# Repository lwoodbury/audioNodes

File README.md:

# audioNodes
Raspberry Pi based Smart Speaker Network designed to run Pure Data patches for sonic arts. 

- small and fairly powerful with good audio quality (I2S 3W amplifier)
- contains a Lipo battery and manages charging via USB micro
- has a smart power switch (safe shutdown and power off)
- everything shared here under Creative Commons Attribution-ShareAlike 4.0 International License, the Raspberry Pi image *, laser cut designs, code and circuit designs. The safe shutdown circuitry and code are inspired by the NeonHorizon/lipopi repo which is covered by a GPL 3.0 licence. Go forth and prosper...

<br />This work is licensed under a <a rel="license" href="http://creativecommons.org/licenses/by-sa/4.0/">Creative Commons Attribution-ShareAlike 4.0 International License</a>.

The idea is to run audio nodes that can communicate with each other using OSC in PD and eventually add sensors and microphone input (and possibly some extra output functionality). The hardware is a development from my digital 'birds' installation: https://www.dotlib.org/home#/forest-of-imagination-2018/

This project is at an early stage and the documentation is not yet as clear as it could be, I have just taken on a new full time job and am not sure when I can next update it or add details on the OSC communication part. Happpy to accept any help in this respect!

To build your own, check out the BOM (bill of materials) spreadsheet for required components and follow the 'Building an Audio Node' document with reference to the 'build stage photos' and notes. The lasercut designs make use of a deep engrave to go around some of the components, you will have to work this out based on your material and laser cutter model.

* Raspberry Pi image can be download from here: https://www.dropbox.com/s/5uapjz6rh7yxo8m/raspbianImage.img.zip?dl=1

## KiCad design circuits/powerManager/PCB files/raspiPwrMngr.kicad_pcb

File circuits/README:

The power management circuit and code was inspired by NeonHorizon's 'lipopi' repo:
https://github.com/NeonHorizon/lipopi

Included here is a stripboard version and a PCB version, currently the case designs are based on the stripboard version. 

Use the file here to make new PCBs; unfortunately the original version of the KiCad project was lost but you can make new gerbers from this one:
..\circuits\powerManager\PCB files\Recovered_LiPoPiShutdown\LiPoPiShutdown.kicad_pcb

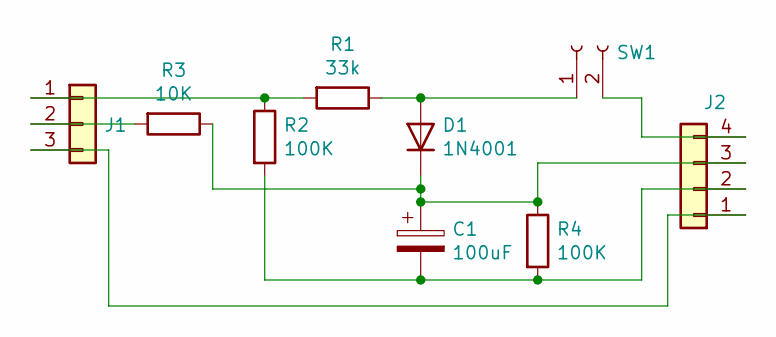
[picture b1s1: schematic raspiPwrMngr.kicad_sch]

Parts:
C1: 100uF; CP_Radial_D8.0mm_P5.00mm
D1: 1N4001; D_DO-41_SOD81_P10.16mm_Horizontal
J1: Conn_01x03; JST_PH_S3B-PH-K_1x03_P2.00mm_Horizontal
J2: Conn_01x04; JST_PH_S4B-PH-K_1x04_P2.00mm_Horizontal
R1: 33k; R_Axial_DIN0207_L6.3mm_D2.5mm_P10.16mm_Horizontal
R2, R4: 100K; R_Axial_DIN0207_L6.3mm_D2.5mm_P10.16mm_Horizontal
R3: 10K; R_Axial_DIN0207_L6.3mm_D2.5mm_P10.16mm_Horizontal
SW1: Conn_01x02_Socket; JST_PH_S2B-PH-K_1x02_P2.00mm_Horizontal

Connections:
unnamed: D1.2 (A), R1.1, SW1.1
unnamed: C1.1, D1.1 (K), J2.3, R3.1, R4.1
unnamed: J1.1, R1.2, R2.1
unnamed: J1.2, R3.2
unnamed: J1.3, J2.1
unnamed: C1.2, J2.2, R2.2, R4.2
unnamed: J2.4, SW1.2

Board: 2 copper layers, 9 parts (0 on the bottom side), 7 nets, no tracks yet.

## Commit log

2020-03-06 First commit
    Need to add support for lfs so can include raspbian image, or just host somewhere
2020-04-23 Added photos
2020-04-23 Update readme
    Add photos and text
2025-06-28 Update circuits with PCB version
    Use the file here to make new PCBs, unfortunately the original version of the KiCad project was lost but you can make new gerbers from this one:
    ..\circuits\powerManager\PCB files\Recovered_LiPoPiShutdown\LiPoPiShutdown.kicad_pcb
2025-07-23 Updated case designs
    Tidied up and archived old files
    Created new svg and cdr files in preparation for power manager pcb
2025-07-23 Update caseUpdated.svg
    Fixed layer order, in prep for power manage pcb
2025-07-24 Rescaled case design
    Seems there was a slight issue with scaling, have rescaled case outer diameter to 85mm
2025-07-27 Created PCB case design
2025-08-09 Reconcile versions
2025-08-09 PCB case reordered, pre shrink
